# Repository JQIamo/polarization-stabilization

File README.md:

# polarization-stabilization
## Project Outline
This project explores polarization drift in optical fibers and methods for an active compensation system with wavelength division multiplexing. The applications are to long distance quantum communication with polarization-encoded photonic qubits.

## Folder Contents
- Reports:
  - PHYS407_Final_Report.pdf: Summary of project progress through December of 2022. This includes the first round of single wavelength measurements and two wavelength(PMD) measurements.
  - FIO_LS Presentation.pptx: presentation given October 2022 at FIO/LS meeting in Rochester NY
- Polarimeter: documentation for telecommunication polarimeter
  - Polarimeter_Manual.pdf: Describes method of operation, how to use and how to calibrate
  - Electronics: KiCad project files for the Teensy motherboard and photodiode transimpedance amplifier boards
  - Motherboard Box: contains part list, front panel cutout and pcb spacers
  - Photodiode Casing Cage Mounted: FreeCAD and .stl files for the photodiode detector housings
- Scripts
- Single wavelength measurements: All single wavelength measurements made from summer 2022 through spring 2023 are included with a jupyter notebook that performs an analysis.
- PMD Wavelength Measurement: two wavelength measurements made in fall 2022 and analysis script

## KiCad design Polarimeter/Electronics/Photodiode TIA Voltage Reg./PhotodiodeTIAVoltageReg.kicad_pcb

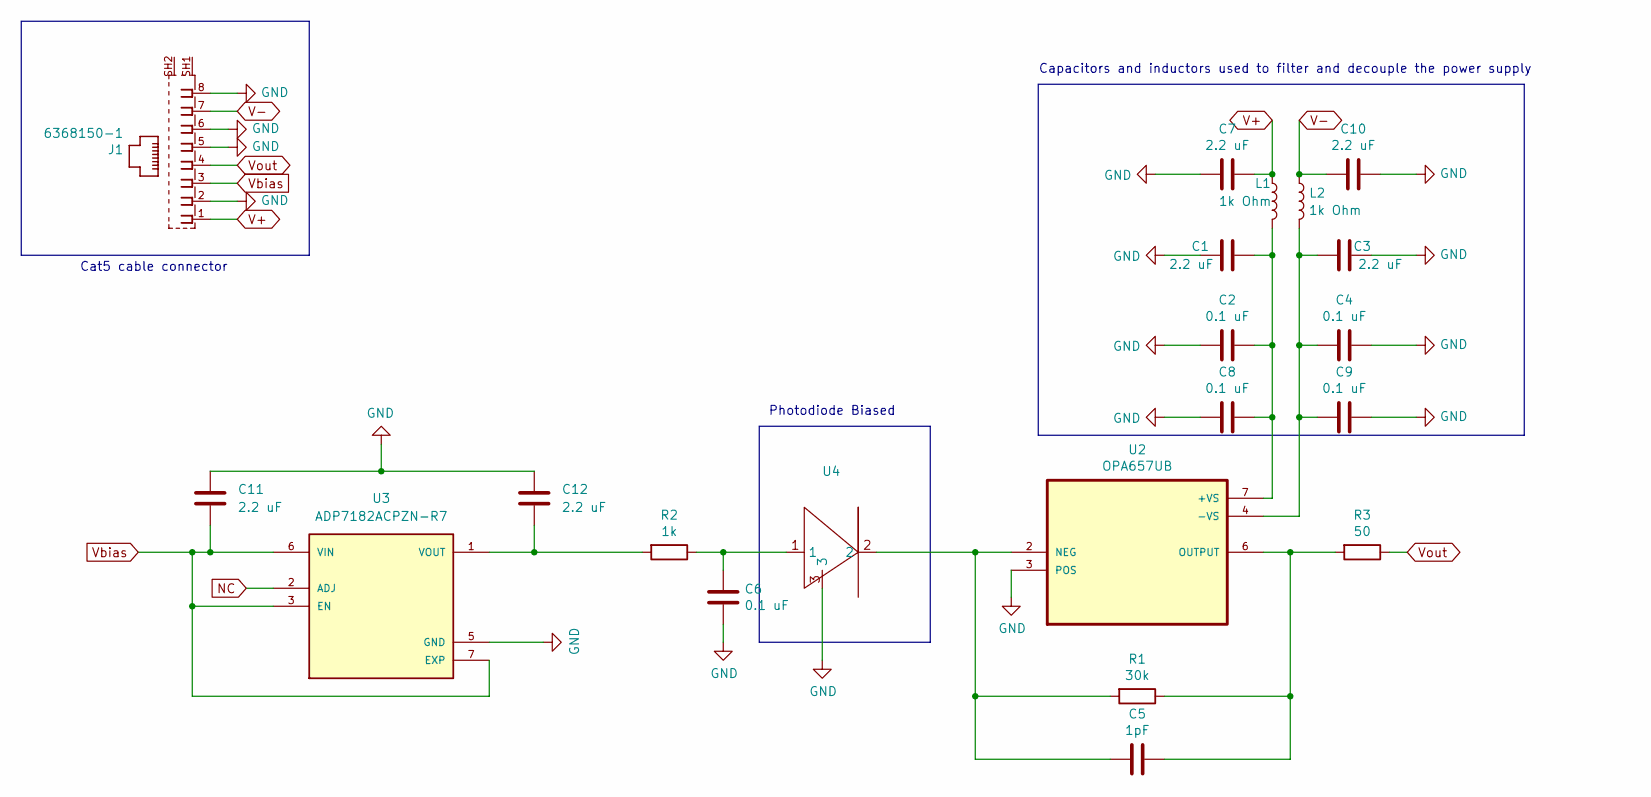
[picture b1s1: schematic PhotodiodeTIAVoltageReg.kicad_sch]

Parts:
C1, C3, C7, C10, C11, C12: 2.2 uF; C_0805_2012Metric
C2, C4, C6, C8, C9: 0.1 uF; C_0603_1608Metric
C5: 1pF; C_0603_1608Metric
J1: 6368150-1; TE_6368150-1
L1, L2: 1k Ohm; L_0603_1608Metric
R1: 30k; R_0603_1608Metric
R2: 1k; R_0603_1608Metric
R3: 50; R_0603_1608Metric
U2: OPA657UB; SOIC127P599X175-8N
U3: ADP7182ACPZN-R7; SON65P200X200X65-7N
U4: (no value)

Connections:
GND: C1.2, C2.2, C3.1, C4.2, C6.2, C7.2, C8.2, C9.2, C10.1, C11.1, C12.1, J1.2, J1.5, J1.6, J1.8, U2.3 (POS), U3.5 (GND), U4.3
NC: U3.2 (ADJ)
unnamed: C1.1, C2.1, C8.1, L1.2, U2.7 (+VS)
unnamed: C3.2, C4.1, C9.1, L2.2, U2.4 (-VS)
unnamed: C5.1, R1.2, U2.2 (NEG), U4.2
unnamed: C5.2, R1.1, R3.2, U2.6 (OUTPUT)
unnamed: C6.1, R2.1, U4.1
unnamed: C12.2, R2.2, U3.1 (VOUT)
V+: C7.1, J1.1, L1.1
V-: C10.2, J1.7, L2.1
Vbias: C11.2, J1.3, U3.3 (EN), U3.6 (VIN), U3.7 (EXP)
Vout: J1.4, R3.1

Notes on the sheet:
Cat5 cable connector
Capacitors and inductors used to filter and decouple the power supply
Photodiode Biased

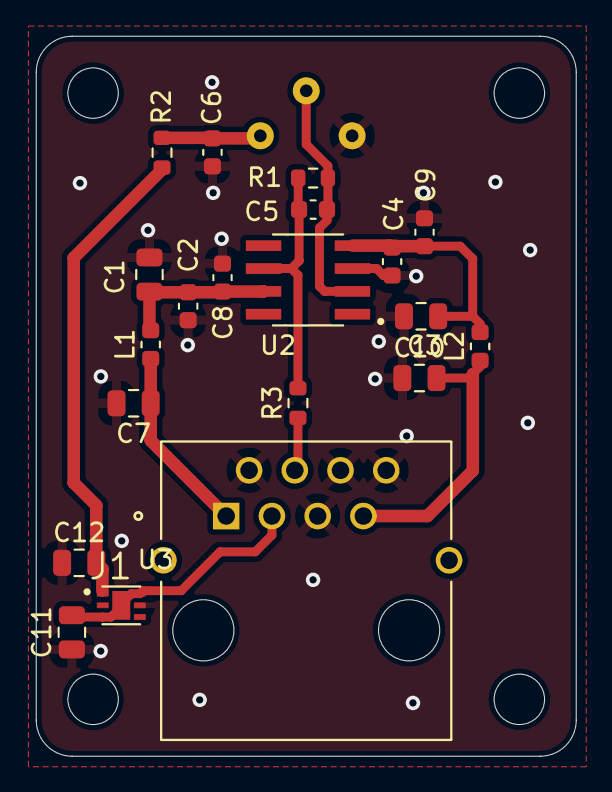
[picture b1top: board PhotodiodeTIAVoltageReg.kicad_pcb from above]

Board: 2 copper layers, 30.0 x 40.0 mm, 21 parts (1 on the bottom side), 11 nets.

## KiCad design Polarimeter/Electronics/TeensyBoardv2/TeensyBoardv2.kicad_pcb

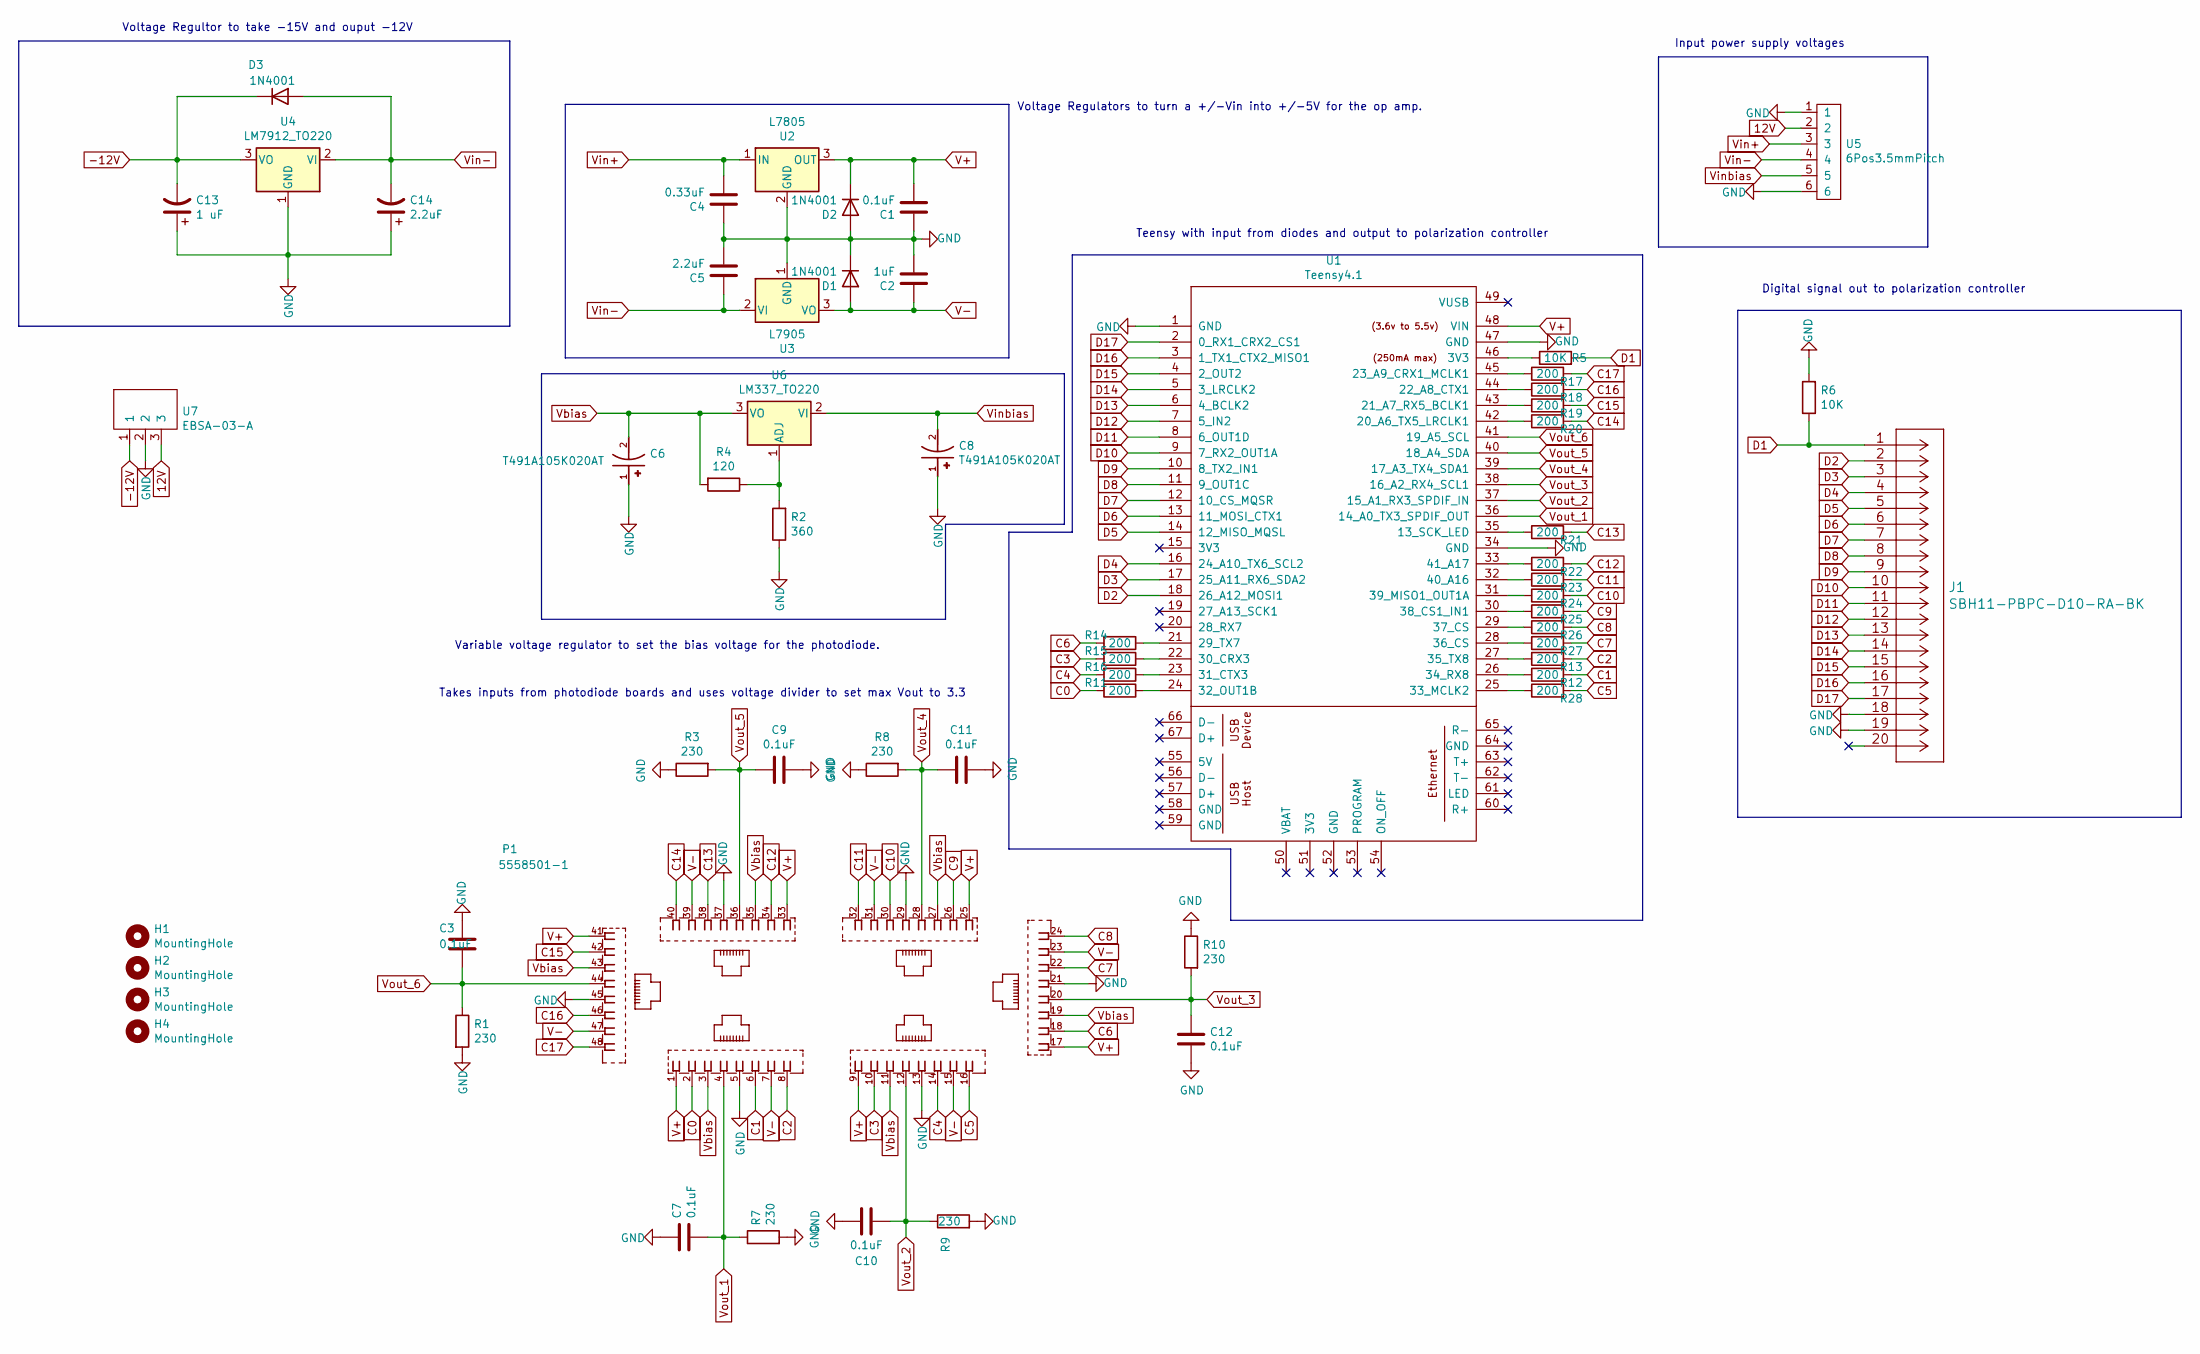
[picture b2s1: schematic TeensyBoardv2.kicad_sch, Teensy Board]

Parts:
C1, C3, C7, C9, C10, C11, C12: 0.1uF; C_0603_1608Metric
C2: 1uF; C_0603_1608Metric
C4: 0.33uF; C_0603_1608Metric
C5: 2.2uF; C_0603_1608Metric
C6, C8: T491A105K020AT; CAPMP3216X180N; PARTREV N/A
C13: 1 uF; CPol_0603_1608Metric
C14: 2.2uF; CPol_0603_1608Metric
D1, D2, D3: 1N4001; D_DO-41_SOD81_P10.16mm_Horizontal
H1, H2, H3, H4: MountingHole; MountingHole_3.5mm
J1: SBH11-PBPC-D10-RA-BK
P1: 5558501-1
R1, R3, R7, R8, R9, R10: 230; R_0603_1608Metric
R2: 360; R_0603_1608Metric
R4: 120; R_0603_1608Metric
R5, R6: 10K; R_0603_1608Metric
R11, R12, R13, R14, R15, R16, R17, R18, R19, R20, R21, R22, R23, R24, R25, R26, R27, R28: 200; R_0603_1608Metric
U1: Teensy4.1; Teensy41
U2: L7805; TO-220F-3_UnderBoardMount
U3: L7905; TO-220F-3_UnderBoardMount
U4: LM7912_TO220; TO-220F-3_UnderBoardMount
U5: 6Pos3.5mmPitch; 6Pos 3.5mmPitch
U6: LM337_TO220; TO-220F-3_UnderBoardMount
U7: EBSA-03-A

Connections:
12V: U5.2, U7.3
-12V: C13.2, D3.1 (K), U4.3 (VO), U7.1
C0: P1.2, R11.2
C1: P1.6, R12.2
C2: P1.8, R13.2
C3: P1.10, R15.2
C4: P1.14, R16.2
C5: P1.16, R28.2
C6: P1.18, R14.2
C7: P1.22, R27.2
C8: P1.24, R26.2
C9: P1.26, R25.2
C10: P1.30, R24.2
C11: P1.32, R23.2
C12: P1.34, R22.2
C13: P1.38, R21.2
C14: P1.40, R20.2
C15: P1.42, R19.2
C16: P1.46, R18.2
C17: P1.48, R17.2
D1: J1.1, R5.2, R6.1
D2: J1.2, U1.18 (26_A12_MOSI1)
D3: J1.3, U1.17 (25_A11_RX6_SDA2)
D4: J1.4, U1.16 (24_A10_TX6_SCL2)
D5: J1.5, U1.14 (12_MISO_MQSL)
D6: J1.6, U1.13 (11_MOSI_CTX1)
D7: J1.7, U1.12 (10_CS_MQSR)
D8: J1.8, U1.11 (9_OUT1C)
D9: J1.9, U1.10 (8_TX2_IN1)
D10: J1.10, U1.9 (7_RX2_OUT1A)
D11: J1.11, U1.8 (6_OUT1D)
D12: J1.12, U1.7 (5_IN2)
D13: J1.13, U1.6 (4_BCLK2)
D14: J1.14, U1.5 (3_LRCLK2)
D15: J1.15, U1.4 (2_OUT2)
D16: J1.16, U1.3 (1_TX1_CTX2_MISO1)
D17: J1.17, U1.2 (0_RX1_CRX2_CS1)
GND: C1.1, C2.2, C3.1, C4.1, C5.2, C6.1, C7.1, C8.1, C9.2, C10.1, C11.2, C12.2, C13.1, C14.1, D1.1 (K), D2.2 (A), J1.18, J1.19, P1.5, P1.13, P1.21, P1.29, P1.37, P1.45, R1.2, R2.1, R3.1, R6.2, R7.2, R8.1, R9.2, R10.1, U1.1 (GND), U1.34 (GND), U1.47 (GND), U2.2 (GND), U3.1 (GND), U4.1 (GND), U5.1, U5.6, U7.2
unnamed: R2.2, R4.1, U6.1 (ADJ)
unnamed: R5.1, U1.46 (3V3)
unnamed: R11.1, U1.24 (32_OUT1B)
unnamed: R12.1, U1.26 (34_RX8)
unnamed: R13.1, U1.27 (35_TX8)
unnamed: R14.1, U1.21 (29_TX7)
unnamed: R15.1, U1.22 (30_CRX3)
unnamed: R16.1, U1.23 (31_CTX3)
unnamed: R17.1, U1.45 (23_A9_CRX1_MCLK1)
unnamed: R18.1, U1.44 (22_A8_CTX1)
unnamed: R19.1, U1.43 (21_A7_RX5_BCLK1)
unnamed: R20.1, U1.42 (20_A6_TX5_LRCLK1)
unnamed: R21.1, U1.35 (13_SCK_LED)
unnamed: R22.1, U1.33 (41_A17)
unnamed: R23.1, U1.32 (40_A16)
unnamed: R24.1, U1.31 (39_MISO1_OUT1A)
unnamed: R25.1, U1.30 (38_CS1_IN1)
unnamed: R26.1, U1.29 (37_CS)
unnamed: R27.1, U1.28 (36_CS)
unnamed: R28.1, U1.25 (33_MCLK2)
V+: C1.2, D2.1 (K), P1.1, P1.9, P1.17, P1.25, P1.33, P1.41, U1.48 (VIN), U2.3 (OUT)
V-: C2.1, D1.2 (A), P1.7, P1.15, P1.23, P1.31, P1.39, P1.47, U3.3 (VO)
Vbias: C6.2, P1.3, P1.11, P1.19, P1.27, P1.35, P1.43, R4.2, U6.3 (VO)
Vin+: C4.2, U2.1 (IN), U5.3
Vin-: C5.1, C14.2, D3.2 (A), U3.2 (VI), U4.2 (VI), U5.4
Vinbias: C8.2, U5.5, U6.2 (VI)
Vout_1: C7.2, P1.4, R7.1, U1.36 (14_A0_TX3_SPDIF_OUT)
Vout_2: C10.2, P1.12, R9.1, U1.37 (15_A1_RX3_SPDIF_IN)
Vout_3: C12.1, P1.20, R10.2, U1.38 (16_A2_RX4_SCL1)
Vout_4: C11.1, P1.28, R8.2, U1.39 (17_A3_TX4_SDA1)
Vout_5: C9.1, P1.36, R3.2, U1.40 (18_A4_SDA)
Vout_6: C3.2, P1.44, R1.1, U1.41 (19_A5_SCL)

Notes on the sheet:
Voltage Regulators to turn a +/-Vin into +/-5V for the op amp.
Input power supply voltages
Variable voltage regulator to set the bias voltage for the photodiode.
Digital signal out to polarization controller
Takes inputs from photodiode boards and uses voltage divider to set max Vout to 3.3
Teensy with input from diodes and output to polarization controller
Voltage Regultor to take -15V and ouput -12V

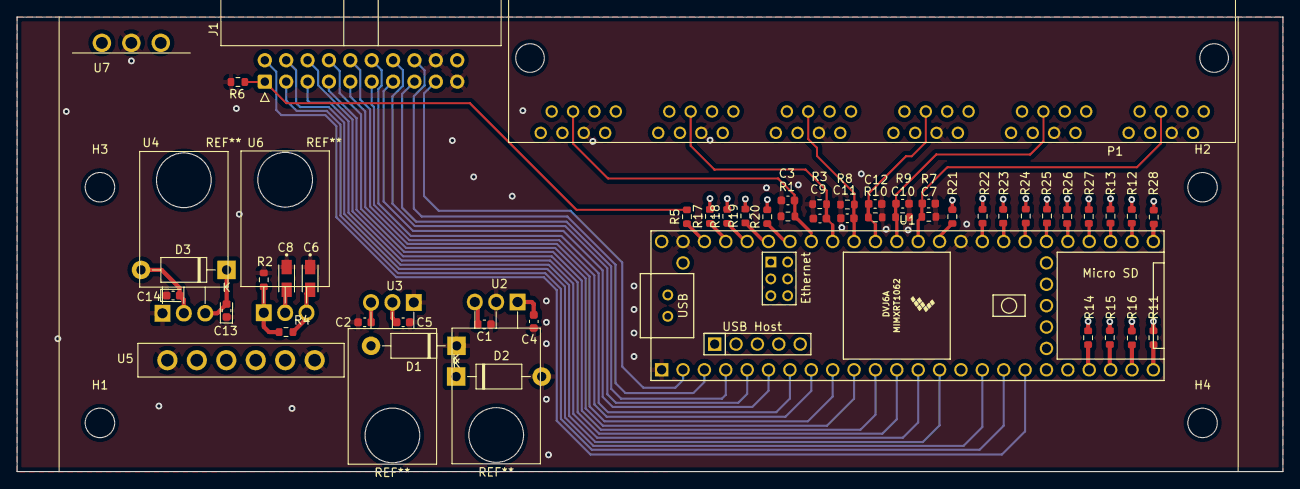
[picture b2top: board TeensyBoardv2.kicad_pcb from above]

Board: 4 copper layers, 150.4 x 54.0 mm, 58 parts (0 on the bottom side), 70 nets.

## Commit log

2023-06-04 Test commit
2023-06-09 add Polarimeter and Single wavelength measurements folders with updated README
2023-06-09 reports folder
2023-06-09 README updated with reports folder
2023-06-09 added tex file and figures for polarimeter manual
